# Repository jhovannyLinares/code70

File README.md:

# Code70

A 70-key split mechanical keyboard (35 keys per half), designed in KiCad and derived from [Lily58 Pro](https://github.com/kata0510/Lily58).

## Features

- Reversible PCB: the same board is used for both halves, selected with jumpers.
- 35 hot-swap sockets per half (Cherry MX / Kailh low profile footprint).
- Pro Micro controller (ATmega32U4).
- 4-pin I2C OLED display.
- TRRS cable between halves.
- SOD-123 diodes, reset button and M2 mounting holes.

## Repository layout

| Folder | Contents |
|---|---|
| `pcb/` | KiCad 5 project (`Code70.pro`), schematic, board and Gerber files |
| `library/` | Footprints and the symbol cache used by the project |
| `case/` | Laser-cut template (`plantilla-corte.ai`, Adobe Illustrator) and board outline (SVG) |
| `layout/` | Key layout spreadsheet (Spanish layout, with `ñ`) |

Library paths are relative to the project (`${KIPRJMOD}/../library`), so `pcb/Code70.pro` opens without extra setup.

## Fabrication

The Gerber files in `pcb/gerber/` and `pcb/Code70_gerber.zip` were exported on 2021-02-12, and the board file was saved again on 2021-02-15. Before ordering, open `pcb/Code70.kicad_pcb` and export the Gerbers again so they match the latest board.

## Firmware

Firmware is not included yet. QMK firmware for this board must define the Code70 matrix; the Sofle keymap does not match it as-is.

## Credits and license

Code70 is released under the MIT License (see `LICENSE`). It builds on Lily58 by Naoki Katahira, which in turn builds on Helix, crkbd and Ergo42, all under the MIT License.

---

## En español

Code70 es un teclado mecánico dividido de 70 teclas (35 por mitad), diseñado en KiCad a partir de Lily58 Pro.

- **PCB reversible:** la misma placa sirve para las dos mitades; se elige con puentes (jumpers).
- **Componentes:** 35 sockets hot-swap por mitad, Pro Micro, pantalla OLED, cable TRRS y botón de reset.
- **Distribución en español:** la hoja `layout/Code70Teclas.xlsx` incluye la `ñ`.
- **Antes de fabricar:** exporta de nuevo los Gerber desde `pcb/Code70.kicad_pcb`; los incluidos son de una revisión anterior de la placa.
- **Firmware:** todavía no está incluido.

Licencia MIT. Basado en Lily58 (Naoki Katahira), que a su vez se basa en Helix, crkbd y Ergo42.

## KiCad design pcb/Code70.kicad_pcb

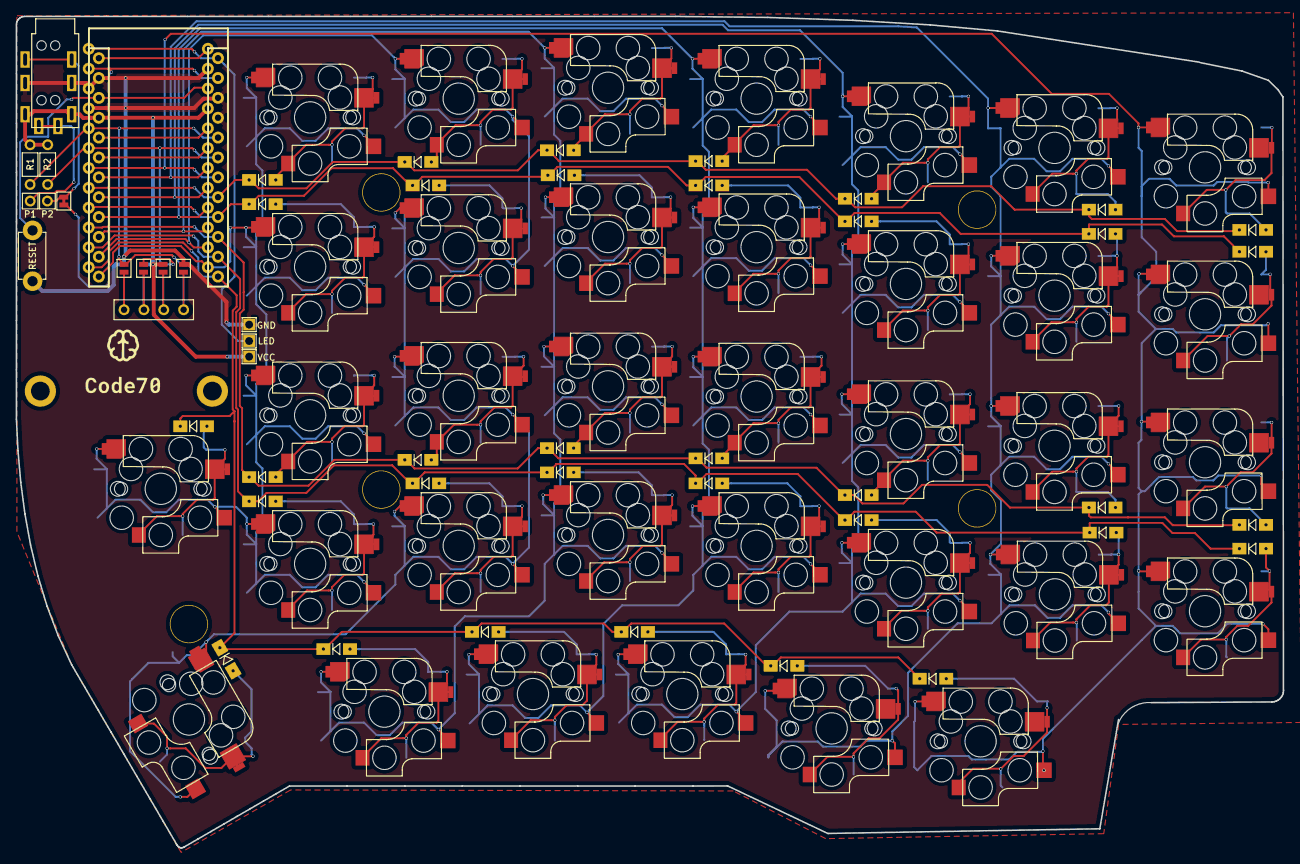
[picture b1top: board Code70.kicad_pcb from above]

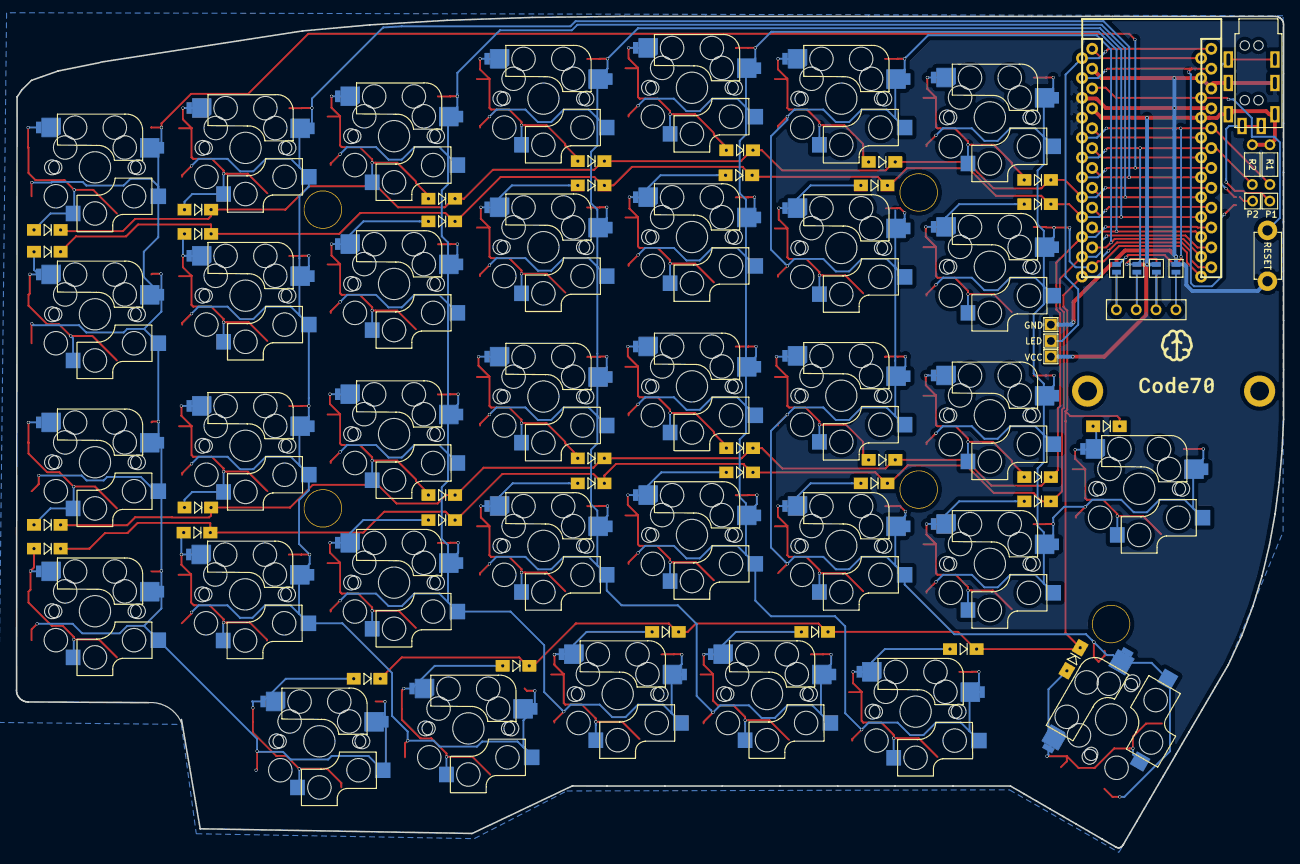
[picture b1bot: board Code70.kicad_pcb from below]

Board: 2 copper layers, 162.1 x 106.3 mm, 95 parts (4 on the bottom side), 60 nets.

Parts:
D1, D2, D3, D4, D5, D6, D7, D8, D9, D10, D11, D12, D13, D14, D15, D16, D17, D18, D19, D20, D21, D22, D23, D24, D25, D26, D27, D28, D29, D30, D31, D32, D33, D34, D35: D; Diode_SOD123
J1: LED
J2: 4PIN; MJ-4PP-9
J3: OLED; OLED_4Pin
JP1, JP2, JP3, JP4, JP5, JP6, JP7, JP8: Jumper_NO_Small; Jumper
P1, P2: i2c_pin; 1pin_conn
R1, R2: R; RESISTOR_mini
RSW1: SW_RST; TACT_SWITCH_TVBP06
SW1, SW2, SW3, SW4, SW5, SW6, SW7, SW8, SW9, SW10, SW11, SW12, SW13, SW14, SW15, SW16, SW17, SW18, SW19, SW20, SW21, SW22, SW23, SW24, SW25, SW26, SW27, SW28, SW29, SW30, SW31, SW32, SW33, SW34, SW35: SW_PUSH; CherryMX_KailhLowProfile_Hotswap
TH1, TH2: HOLE; M2_HOLE_PCB
TH3, TH4, TH5, TH6, TH7: HOLE; HOLE_M2_TH
U1: ProMicro; ProMicro_rev2
W1: jumper; jumper_data

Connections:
DATA: U1.2, W1.1
GND: J1.3, J2.2, JP1.2, JP8.2, RSW1.1, U1.3, U1.4, U1.23
LED: J1.2, U1.1
unnamed: D1.2, SW1.2
unnamed: D2.2, SW2.2
unnamed: D3.2, SW3.2
unnamed: D4.2, SW4.2
unnamed: D5.2, SW5.2
unnamed: D6.2, SW6.2
unnamed: D7.2, SW7.2
unnamed: D8.2, SW8.2
unnamed: D9.2, SW9.2
unnamed: D10.2, SW10.2
unnamed: D11.2, SW11.2
unnamed: D12.2, SW12.2
unnamed: D13.2, SW13.2
unnamed: D14.2, SW14.2
unnamed: D15.2, SW15.2
unnamed: D16.2, SW16.2
unnamed: D17.2, SW17.2
unnamed: D18.2, SW18.2
unnamed: D19.2, SW19.2
unnamed: D20.2, SW20.2
unnamed: D21.2, SW21.2
unnamed: D22.2, SW22.2
unnamed: D23.2, SW23.2
unnamed: D24.2, SW24.2
unnamed: D25.2, SW25.2
unnamed: D26.2, SW26.2
unnamed: D27.2, SW27.2
unnamed: D28.2, SW28.2
unnamed: D29.2, SW29.2
unnamed: D30.2, SW30.2
unnamed: D31.2, SW31.2
unnamed: D32.2, SW32.2
unnamed: D33.2, SW33.2
unnamed: D34.2, SW34.2
unnamed: D35.2, SW35.2
unnamed: J2.3, P2.1, W1.2
unnamed: J2.4, P1.1
unnamed: J3.1, JP4.1, JP8.1
unnamed: J3.2, JP3.1, JP7.1
unnamed: J3.3, JP2.1, JP6.1
unnamed: J3.4, JP1.1, JP5.1
RESET: RSW1.2, U1.22
SCL: JP3.2, JP6.2, R2.2, U1.6
SDA: JP4.2, JP5.2, R1.2, U1.5
VCC: J1.1, J2.1, JP2.2, JP7.2, R1.1, R2.1, U1.21
col0: SW6.1, SW12.1, SW18.1, SW24.1, SW30.1, U1.18
col1: SW5.1, SW11.1, SW17.1, SW23.1, SW29.1, U1.17
col2: SW4.1, SW10.1, SW16.1, SW22.1, SW28.1, U1.16
col3: SW3.1, SW9.1, SW15.1, SW21.1, SW27.1, U1.15
col4: SW2.1, SW8.1, SW14.1, SW20.1, SW26.1, U1.14
col5: SW1.1, SW7.1, SW13.1, SW19.1, SW25.1, U1.13
col6: SW31.1, SW32.1, SW33.1, SW34.1, SW35.1, U1.7
row0: D1.1, D2.1, D3.1, D4.1, D5.1, D6.1, D31.1, U1.8
row1: D7.1, D8.1, D9.1, D10.1, D11.1, D12.1, D32.1, U1.9
row2: D13.1, D14.1, D15.1, D16.1, D17.1, D18.1, D33.1, U1.10
row3: D19.1, D20.1, D21.1, D22.1, D23.1, D24.1, D34.1, U1.11
row4: D25.1, D26.1, D27.1, D28.1, D29.1, D30.1, D35.1, U1.12
